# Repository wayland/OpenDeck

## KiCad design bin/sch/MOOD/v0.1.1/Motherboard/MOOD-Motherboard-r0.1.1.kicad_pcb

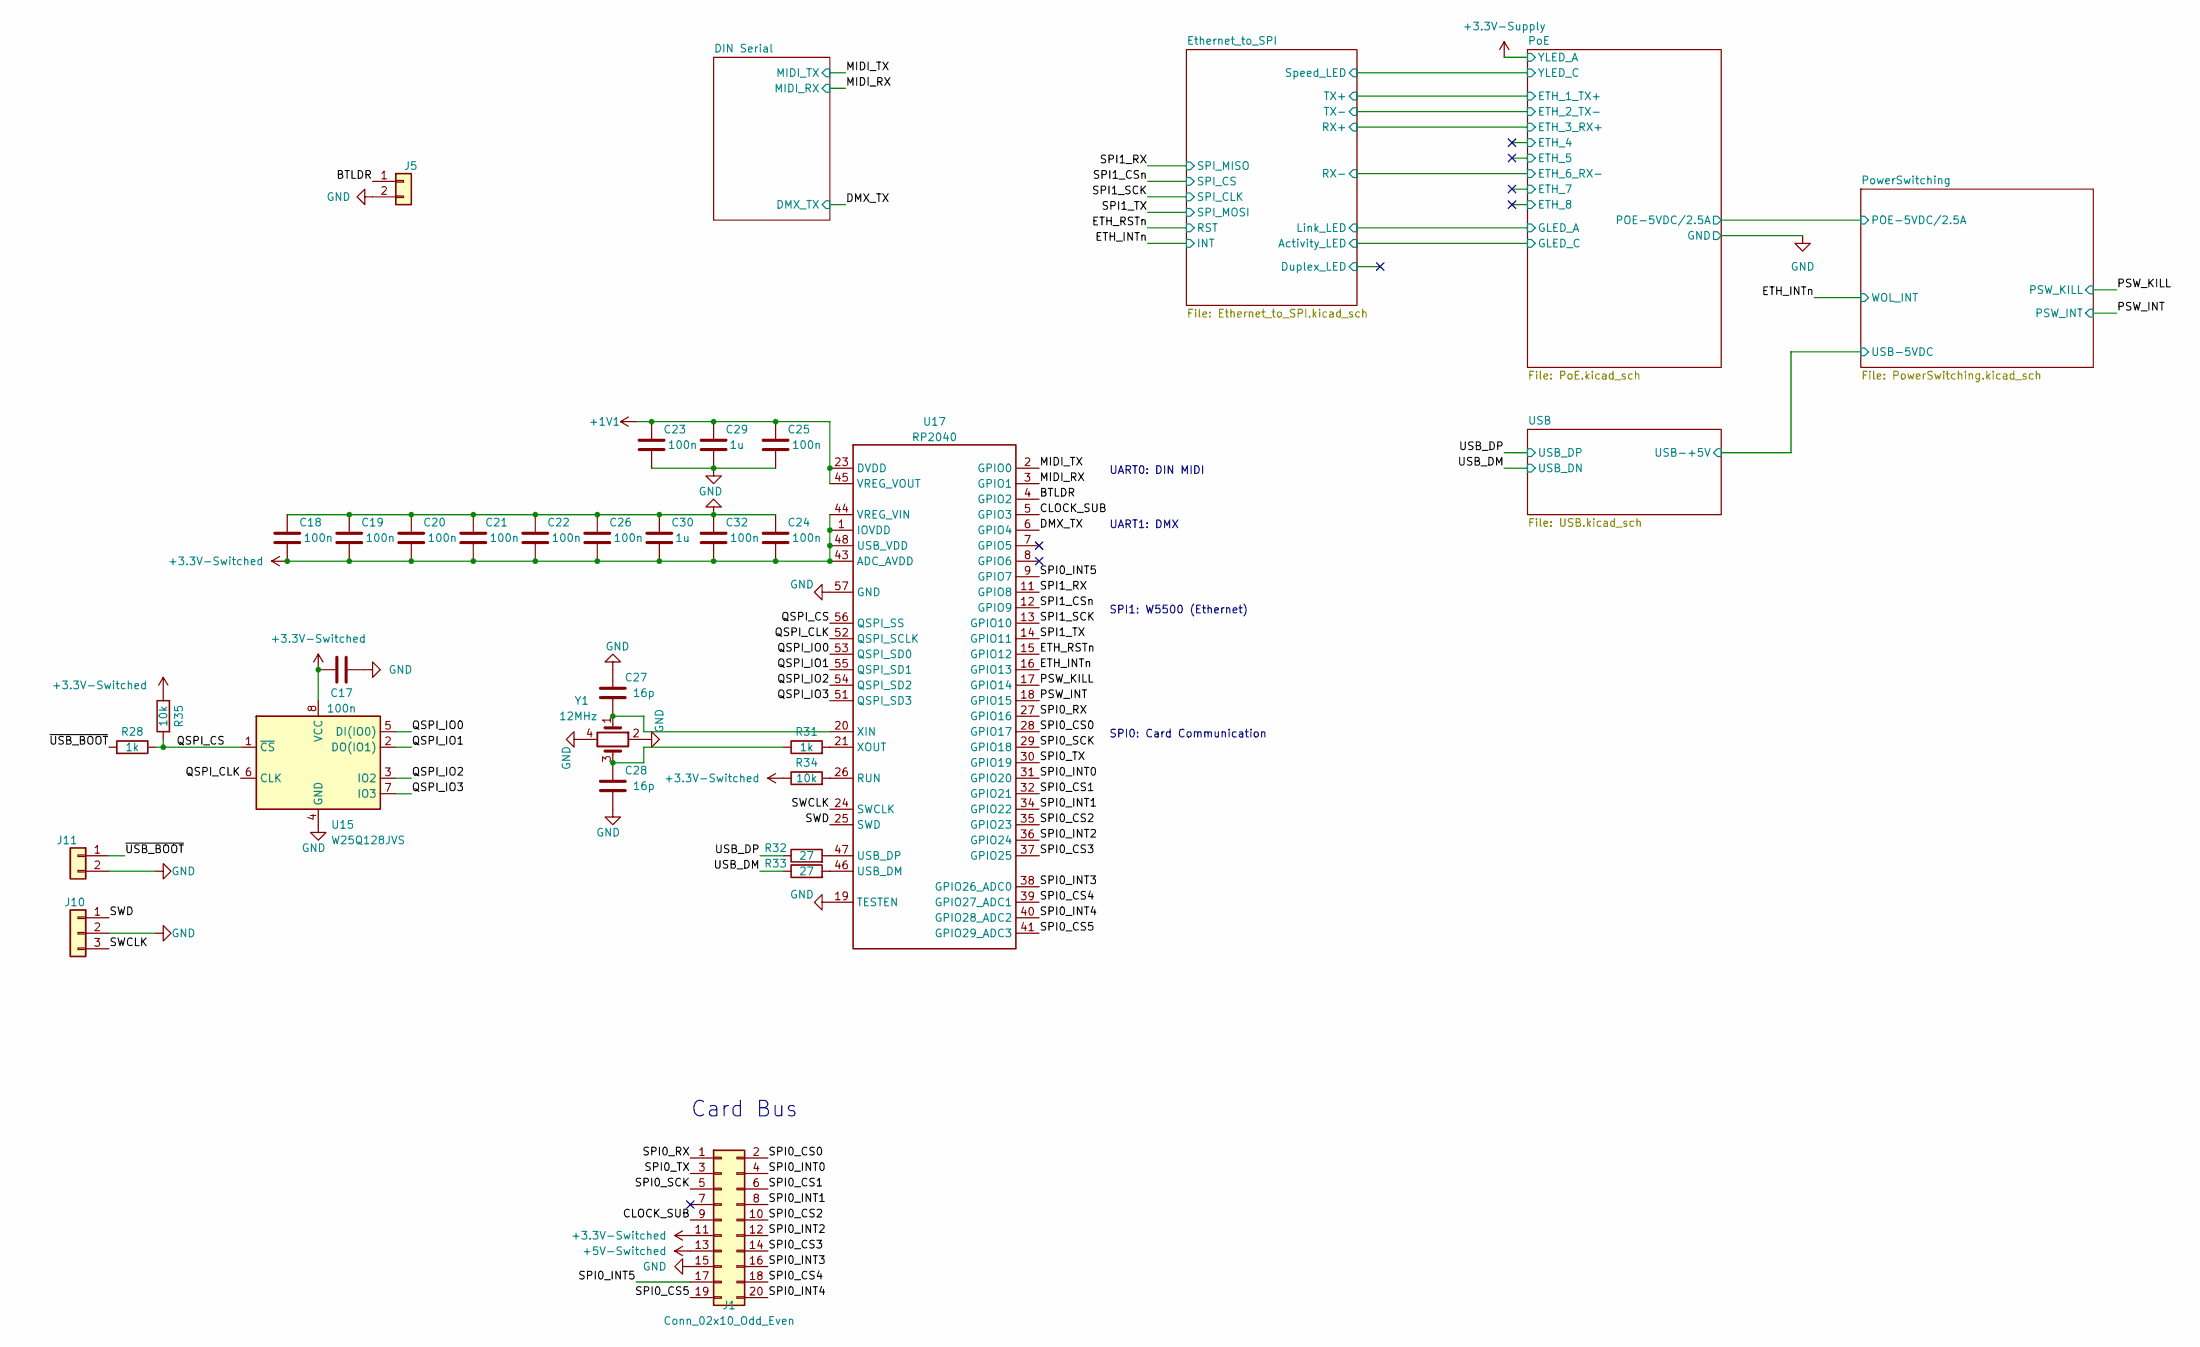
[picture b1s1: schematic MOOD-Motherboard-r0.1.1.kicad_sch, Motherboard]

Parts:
C17, C18, C19, C20, C21, C22, C23, C24, C25, C26, C32: 100n; C_0402_1005Metric; LCSC C1525
C27, C28: 16p; C_0402_1005Metric; LCSC C161307
C29, C30: 1u; C_0402_1005Metric; LCSC C52923
J1: Conn_02x10_Odd_Even; PinHeader_2x10_P2.54mm_Vertical
J5, J11: Conn_01x02; PinHeader_1x02_P2.54mm_Vertical
J10: Conn_01x03; PinHeader_1x03_P2.54mm_Vertical
R28, R31: 1k; R_0402_1005Metric; LCSC C11702
R32, R33: 27; R_0402_1005Metric; LCSC C25100
R34, R35: 10k; R_0402_1005Metric; LCSC C25744
U15: W25Q128JVS; SOIC-8_5.23x5.23mm_P1.27mm
U17: RP2040; QFN-56-1EP_7x7mm_P0.4mm_EP3.2x3.2mm; LCSC C2040
Y1: 12MHz; Crystal_SMD_2520-4Pin_2.5x2.0mm; LCSC C254355

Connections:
+1V1: C23.2, C25.2, C29.2, U17.23 (DVDD), U17.45 (VREG_VOUT), U17.50 (DVDD)
+3.3V-Switched: C17.1, C18.1, C19.1, C20.1, C21.1, C22.1, C24.1, C26.1, C30.1, C32.1, J1.11, R34.1, R35.1, U15.8 (VCC), U17.1 (IOVDD), U17.10 (IOVDD), U17.22 (IOVDD), U17.33 (IOVDD), U17.42 (IOVDD), U17.43 (ADC_AVDD), U17.44 (VREG_VIN), U17.48 (USB_VDD), U17.49 (IOVDD); also elsewhere on the board
+5V-Switched: J1.13; also elsewhere on the board
/BTLDR: J5.1, U17.4 (GPIO2)
/CLOCK_SUB: J1.9, U17.5 (GPIO3)
/DMX_TX: U17.6 (GPIO4); also elsewhere on the board
/ETH_INTn: U17.16 (GPIO13); also elsewhere on the board
/ETH_RSTn: U17.15 (GPIO12); also elsewhere on the board
/MIDI_RX: U17.3 (GPIO1); also elsewhere on the board
/MIDI_TX: U17.2 (GPIO0); also elsewhere on the board
/PSW_INT: U17.18 (GPIO15); also elsewhere on the board
/PSW_KILL: U17.17 (GPIO14); also elsewhere on the board
/QSPI_CLK: U15.6 (CLK), U17.52 (QSPI_SCLK)
/QSPI_CS: R28.1, R35.2, U15.1 (~CS), U17.56 (QSPI_SS)
/QSPI_IO0: U15.5 (DI(IO0)), U17.53 (QSPI_SD0)
/QSPI_IO1: U15.2 (DO(IO1)), U17.55 (QSPI_SD1)
/QSPI_IO2: U15.3 (IO2), U17.54 (QSPI_SD2)
/QSPI_IO3: U15.7 (IO3), U17.51 (QSPI_SD3)
/SPI0_CS0: J1.2, U17.28 (GPIO17)
/SPI0_CS1: J1.6, U17.32 (GPIO21)
/SPI0_CS2: J1.10, U17.35 (GPIO23)
/SPI0_CS3: J1.14, U17.37 (GPIO25)
/SPI0_CS4: J1.18, U17.39 (GPIO27_ADC1)
/SPI0_CS5: J1.19, U17.41 (GPIO29_ADC3)
/SPI0_INT0: J1.4, U17.31 (GPIO20)
/SPI0_INT1: J1.8, U17.34 (GPIO22)
/SPI0_INT2: J1.12, U17.36 (GPIO24)
/SPI0_INT3: J1.16, U17.38 (GPIO26_ADC0)
/SPI0_INT4: J1.20, U17.40 (GPIO28_ADC2)
/SPI0_INT5: J1.17, U17.9 (GPIO7)
/SPI0_RX: J1.1, U17.27 (GPIO16)
/SPI0_SCK: J1.5, U17.29 (GPIO18)
/SPI0_TX: J1.3, U17.30 (GPIO19)
/SPI1_CSn: U17.12 (GPIO9); also elsewhere on the board
/SPI1_RX: U17.11 (GPIO8); also elsewhere on the board
/SPI1_SCK: U17.13 (GPIO10); also elsewhere on the board
/SPI1_TX: U17.14 (GPIO11); also elsewhere on the board
/SWCLK: J10.3, U17.24 (SWCLK)
/SWD: J10.1, U17.25 (SWD)
/USB_DM: R33.1; also elsewhere on the board
/USB_DP: R32.1; also elsewhere on the board
/~USB_BOOT: J11.1, R28.2
unnamed: C27.1, U17.20 (XIN), Y1.1
unnamed: C28.2, R31.1, Y1.3
unnamed: R31.2, U17.21 (XOUT)
unnamed: R32.2, U17.47 (USB_DP)
unnamed: R33.2, U17.46 (USB_DM)
unnamed: R34.2, U17.26 (RUN)

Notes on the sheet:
Card Bus
UART1: DMX
UART0: DIN MIDI
SPI1: W5500 (Ethernet)
SPI0: Card Communication

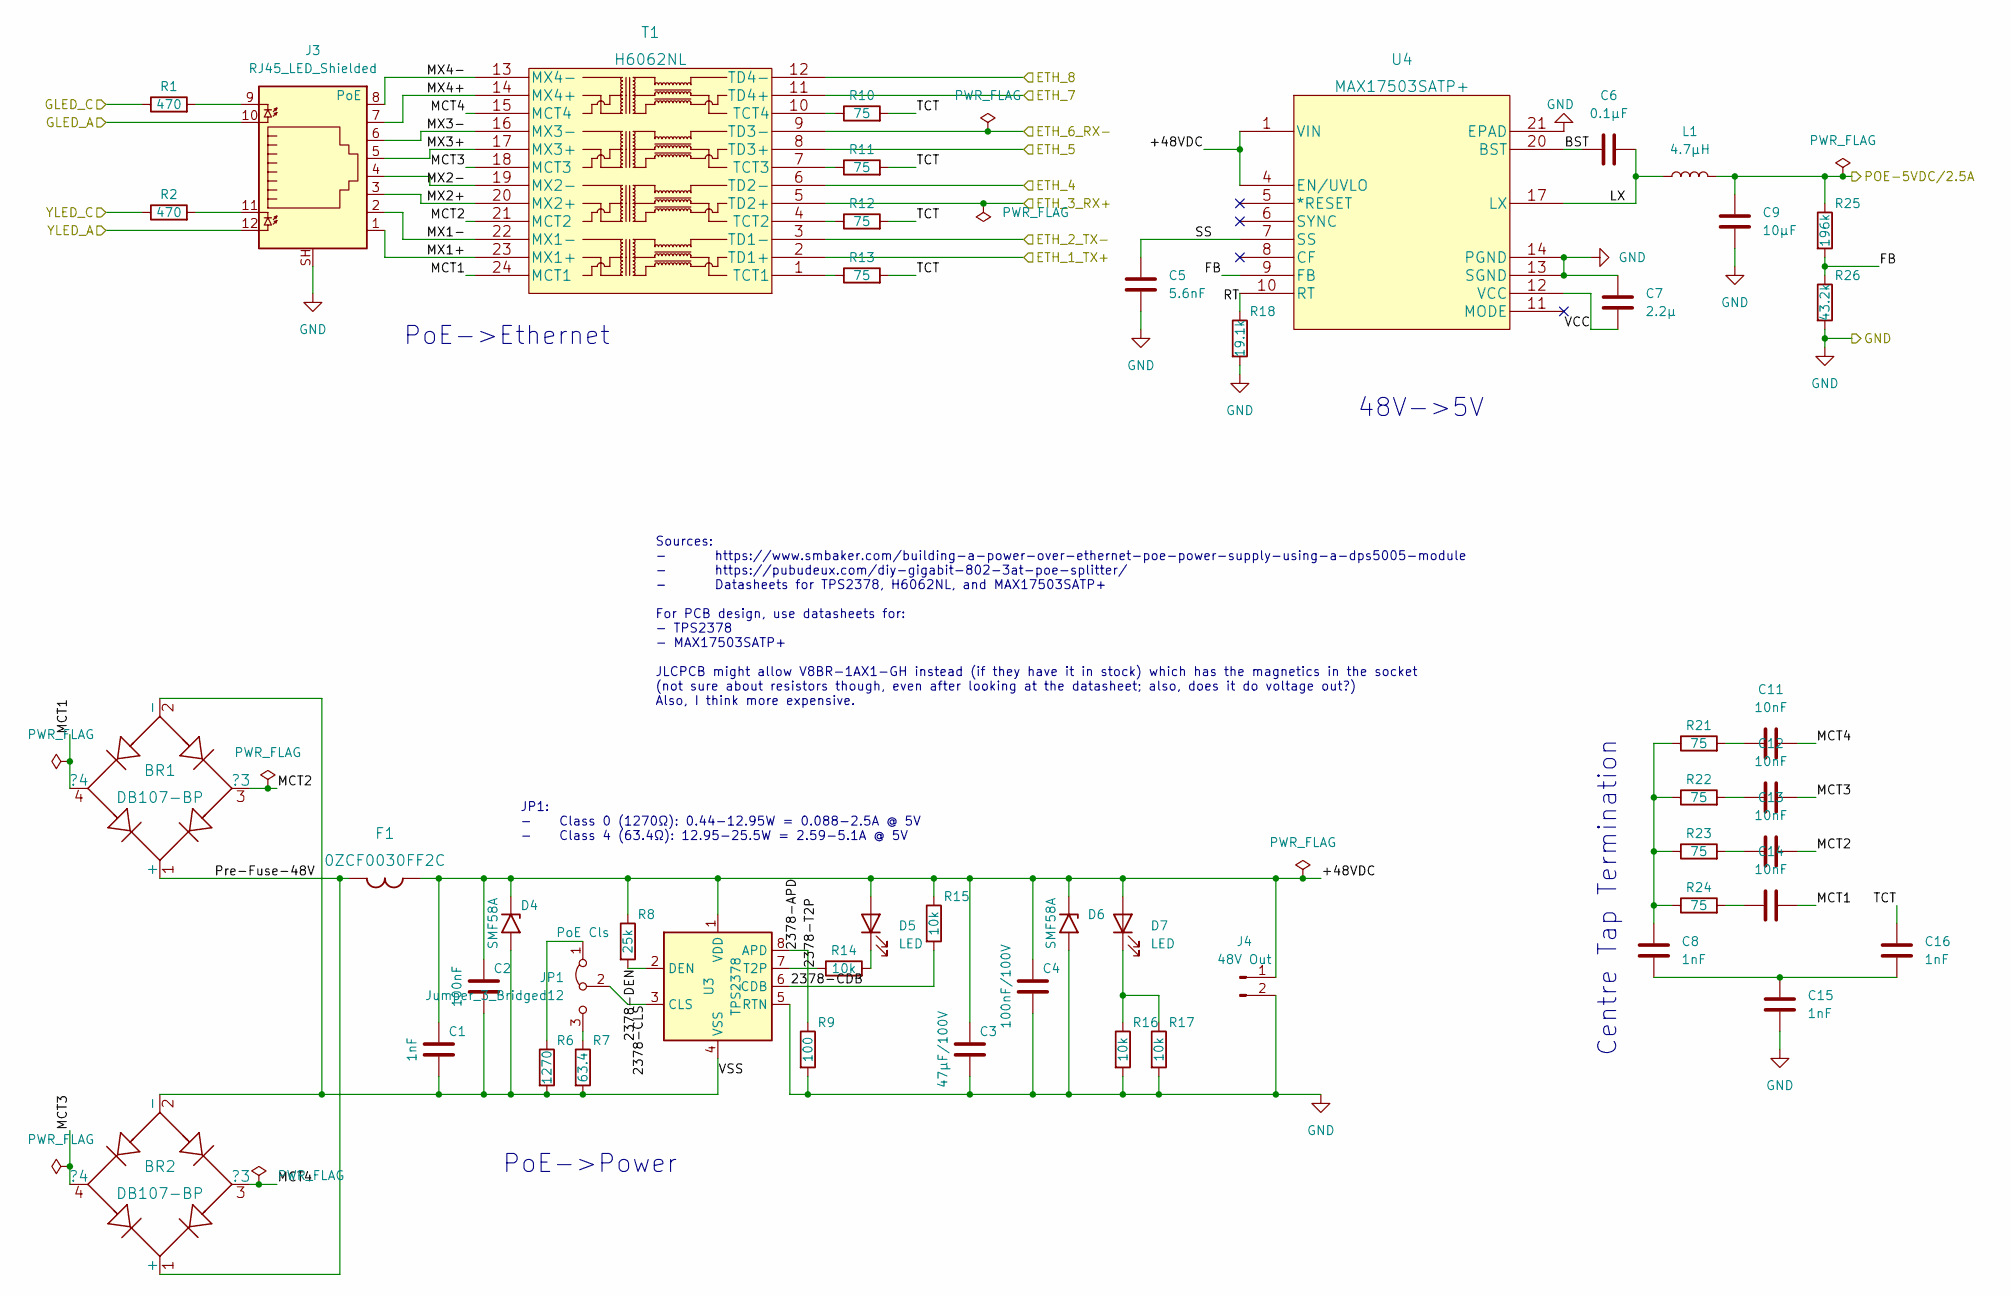
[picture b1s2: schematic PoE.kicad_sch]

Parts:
BR1, BR2: DB107-BP; DB-1_MCC
C1, C8, C15, C16: 1nF; C_0402_1005Metric
C2: 100nF; C_0402_1005Metric
C3: 47μF/100V; C_0402_1005Metric
C4: 100nF/100V; C_0402_1005Metric
C5: 5.6nF; C_0402_1005Metric
C6: 0.1μF; C_0402_1005Metric
C7: 2.2μ; C_0402_1005Metric
C9: 10μF; C_0402_1005Metric
C11, C12, C13, C14: 10nF; C_0402_1005Metric
D4, D6: SMF58A; D_SMF
D5, D7: LED; LED_0805_2012Metric
F1: 0ZCF0030FF2C
J3: RJ45_LED_Shielded; RJ45_BEL_SS74301-00x_Vertical
J4: 48V Out; PinHeader_1x02_P2.54mm_Vertical
JP1: Jumper_3_Bridged12; PinHeader_1x03_P2.54mm_Vertical
L1: 4.7μH; L_0201_0603Metric
R1, R2: 470; R_0402_1005Metric
R6: 1270; R_0402_1005Metric
R7: 63.4; R_0402_1005Metric
R8: 25k; R_0402_1005Metric
R9: 100; R_0402_1005Metric
R10, R11, R12, R13, R21, R22, R23, R24: 75; R_0402_1005Metric
R14, R15, R16, R17: 10k; R_0402_1005Metric
R18: 19.1k; R_0402_1005Metric
R25: 196k; R_0402_1005Metric
R26: 43.2k; R_0402_1005Metric
T1: H6062NL; H6062FNLT_PUL
U3: TPS2378; Texas_HSOP-8-1EP_3.9x4.9mm_P1.27mm_ThermalVias
U4: MAX17503SATP+; 21-100172_T2044+4C_MXM

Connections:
+3.3V-Supply: J3.12; also elsewhere on the board
/Ethernet_to_SPI/Activity_LED: R1.1; also elsewhere on the board
/Ethernet_to_SPI/Link_LED: J3.10; also elsewhere on the board
/Ethernet_to_SPI/RX+: T1.5 (TD2+); also elsewhere on the board
/Ethernet_to_SPI/RX-: T1.9 (TD3-); also elsewhere on the board
/Ethernet_to_SPI/Speed_LED: R2.1; also elsewhere on the board
/Ethernet_to_SPI/TX+: T1.2 (TD1+); also elsewhere on the board
/Ethernet_to_SPI/TX-: T1.3 (TD1-); also elsewhere on the board
/PoE/2378-APD: R9.1, U3.8 (APD)
/PoE/2378-CDB: R15.2, U3.6 (CDB)
/PoE/2378-CLS: JP1.2 (C), U3.3 (CLS)
/PoE/2378-DEN: R8.2, U3.2 (DEN)
/PoE/2378-T2P: R14.1, U3.7 (T2P)
/PoE/+48VDC: C1.1, C2.1, C3.1, C4.1, D4.1 (A1), D5.2 (A), D6.1 (A1), D7.2 (A), F1.2, J4.1, R8.1, R15.1, U3.1 (VDD), U4.1 (VIN), U4.2 (VIN), U4.3 (VIN), U4.4 (EN/UVLO)
/PoE/BST: C6.1, U4.20 (BST)
/PoE/ETH_4: T1.6 (TD2-)
/PoE/ETH_5: T1.8 (TD3+)
/PoE/ETH_7: T1.11 (TD4+)
/PoE/ETH_8: T1.12 (TD4-)
/PoE/FB: R25.2, R26.1, U4.9 (FB)
/PoE/LX: C6.2, L1.1, U4.17 (LX), U4.18 (LX), U4.19 (LX)
/PoE/MCT1: BR1.4 (?4), C14.2, T1.24 (MCT1)
/PoE/MCT2: BR1.3 (?3), C13.2, T1.21 (MCT2)
/PoE/MCT3: BR2.4 (?4), C12.2, T1.18 (MCT3)
/PoE/MCT4: BR2.3 (?3), C11.2, T1.15 (MCT4)
/PoE/MX1+: J3.1, T1.23 (MX1+)
/PoE/MX1-: J3.2, T1.22 (MX1-)
/PoE/MX2+: J3.3, T1.20 (MX2+)
/PoE/MX2-: J3.4, T1.19 (MX2-)
/PoE/MX3+: J3.5, T1.17 (MX3+)
/PoE/MX3-: J3.6, T1.16 (MX3-)
/PoE/MX4+: J3.7, T1.14 (MX4+)
/PoE/MX4-: J3.8, T1.13 (MX4-)
/PoE/POE-5VDC/2.5A: C9.1, L1.2, R25.1; also elsewhere on the board
/PoE/Pre-Fuse-48V: BR1.1 (+), BR2.1 (+), F1.1
/PoE/RT: R18.1, U4.10 (RT)
/PoE/SS: C5.1, U4.7 (SS)
/PoE/TCT: C16.1, R10.2, R11.2, R12.2, R13.2
/PoE/VCC: C7.2, U4.12 (VCC)
EPAD: BR1.2 (-), BR2.2 (-), C1.2, C2.2, D4.2 (A2), R6.2, R7.2, U3.4 (VSS), U3.9 (EPAD)
unnamed: C8.1, R21.1, R22.1, R23.1, R24.1
unnamed: C11.1, R21.2
unnamed: C12.1, R22.2
unnamed: C13.1, R23.2
unnamed: C14.1, R24.2
unnamed: C8.2, C15.1, C16.2
unnamed: D5.1 (K), R14.2
unnamed: D7.1 (K), R16.1, R17.1
unnamed: J3.9, R1.2
unnamed: J3.11, R2.2
unnamed: JP1.1 (A), R6.1
unnamed: JP1.3 (B), R7.1
unnamed: R10.1, T1.10 (TCT4)
unnamed: R11.1, T1.7 (TCT3)
unnamed: R12.1, T1.4 (TCT2)
unnamed: R13.1, T1.1 (TCT1)

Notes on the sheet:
PoE->Power
Sources: - https://www.smbaker.com/building-a-power-over-ethernet-poe-power-supply-using-a-dps5005-module - https://pubudeux.com/diy-gigabit-802-3at-poe-splitter/ - Datasheets for TPS2378, H6062NL, and MAX17503SATP+ For PCB design, use datasheets for: - TPS2378 - MAX17503SATP+ JLCPCB might allow V8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
JP1: - Class 0 (1270Ω): 0.44-12.95W = 0.088-2.5A @ 5V - Class 4 (63.4Ω): 12.95-25.5W = 2.59-5.1A @ 5V
48V->5V
Centre Tap Termination
PoE->Ethernet

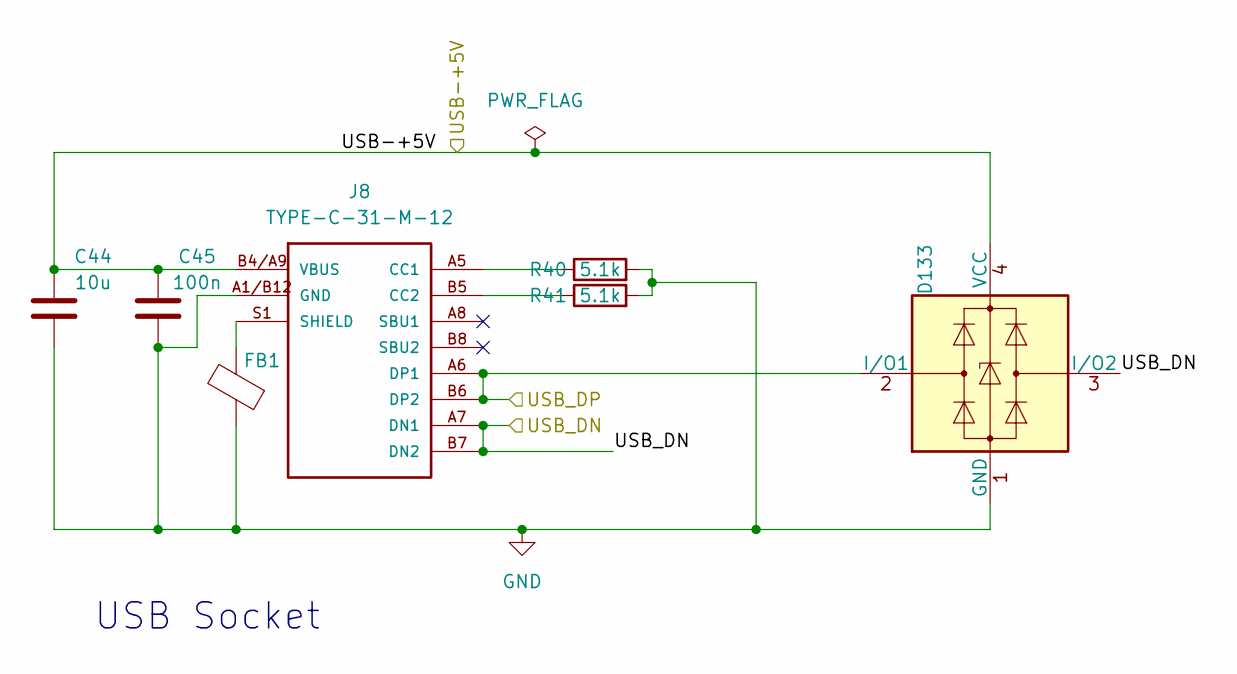
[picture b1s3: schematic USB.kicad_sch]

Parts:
C44: 10u; C_0402_1005Metric; LCSC C15525
C45: 100n; C_0402_1005Metric; LCSC C1525
D133: PRTR5V0U2X; SOT-143; LCSC C2827688
FB1: FerriteBead; R_0805_2012Metric; LCSC C85840
J8: TYPE-C-31-M-12; PARTREV 2020.12.08; LCSC C165948
R40, R41: 5.1k; R_0402_1005Metric; LCSC C25905

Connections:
/USB_DM: D133.3 (I/O2), J8.A7 (DN1), J8.B7 (DN2); also elsewhere on the board
/USB_DP: D133.2 (I/O1), J8.A6 (DP1), J8.B6 (DP2); also elsewhere on the board
unnamed: FB1.2, J8.S1 (SHIELD), J8.S2 (SHIELD), J8.S3 (SHIELD), J8.S4 (SHIELD)
unnamed: J8.A5 (CC1), R40.1
unnamed: J8.B5 (CC2), R41.1
VBUS: C44.2, C45.2, D133.4 (VCC), J8.A4/B9 (VBUS), J8.B4/A9 (VBUS); also elsewhere on the board

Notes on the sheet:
USB Socket

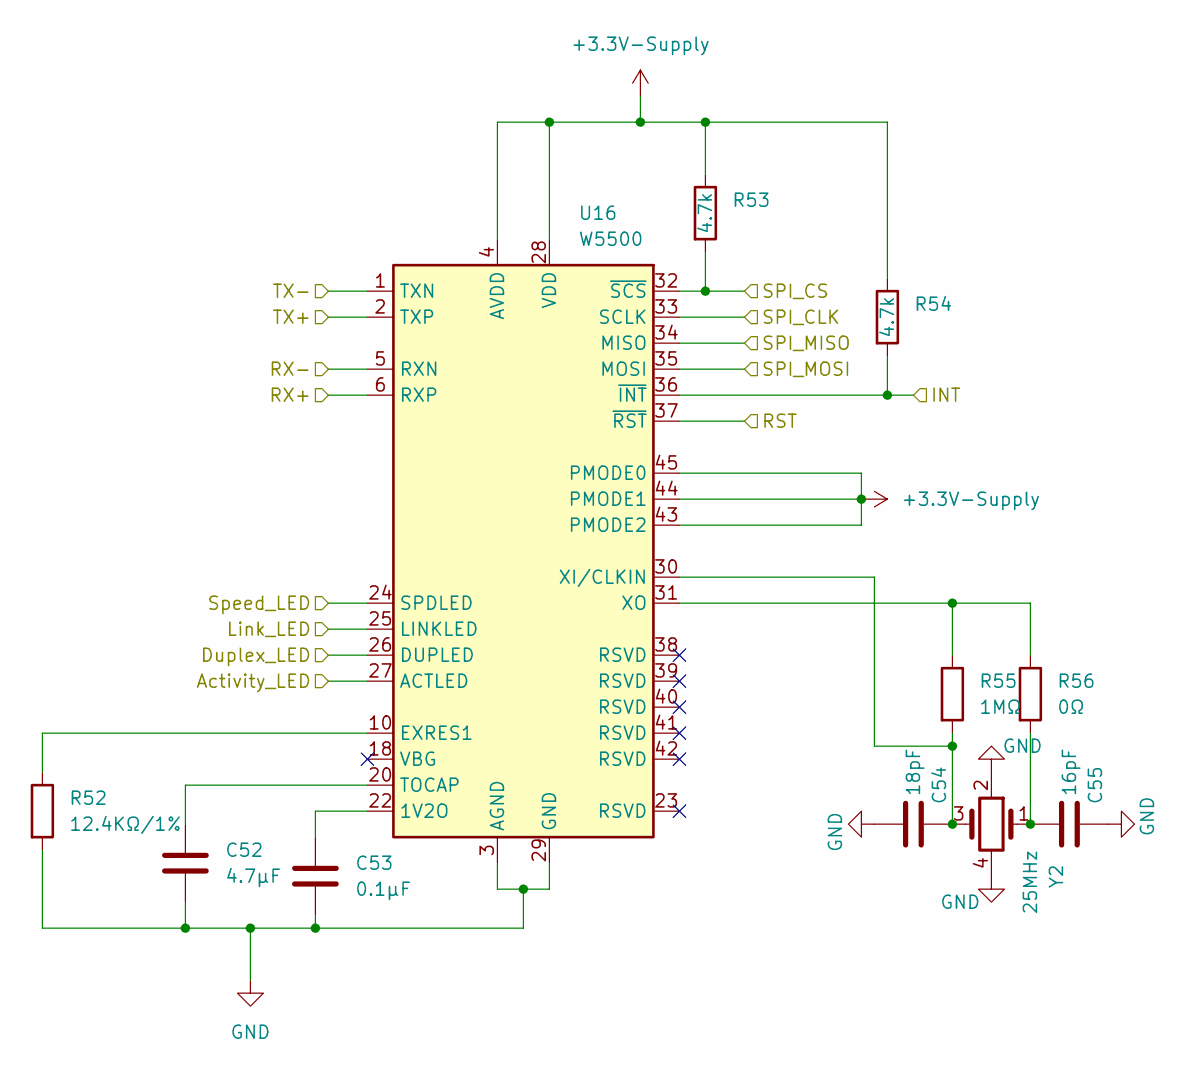
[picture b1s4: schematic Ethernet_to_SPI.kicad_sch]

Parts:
C52: 4.7μF; C_0402_1005Metric
C53: 0.1μF; C_0402_1005Metric
C54: 18pF; C_0402_1005Metric; LCSC C161307
C55: 16pF; C_0402_1005Metric; LCSC C161307
R52: 12.4KΩ/1%; R_0402_1005Metric
R53, R54: 4.7k; R_0402_1005Metric
R55: 1MΩ; R_0402_1005Metric
R56: 0Ω; R_0402_1005Metric
U16: W5500; LQFP-48_7x7mm_P0.5mm
Y2: 25MHz; Crystal_SMD_2520-4Pin_2.5x2.0mm; LCSC C254355

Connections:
+3.3V-Supply: R53.1, R54.1, U16.4 (AVDD), U16.8 (AVDD), U16.11 (AVDD), U16.15 (AVDD), U16.17 (AVDD), U16.21 (AVDD), U16.28 (VDD), U16.43 (PMODE2), U16.44 (PMODE1), U16.45 (PMODE0); also elsewhere on the board
/ETH_INTn: R54.2, U16.36 (~INT); also elsewhere on the board
/ETH_RSTn: U16.37 (~RST); also elsewhere on the board
/Ethernet_to_SPI/Activity_LED: U16.27 (ACTLED); also elsewhere on the board
/Ethernet_to_SPI/Duplex_LED: U16.26 (DUPLED)
/Ethernet_to_SPI/Link_LED: U16.25 (LINKLED); also elsewhere on the board
/Ethernet_to_SPI/RX+: U16.6 (RXP); also elsewhere on the board
/Ethernet_to_SPI/RX-: U16.5 (RXN); also elsewhere on the board
/Ethernet_to_SPI/Speed_LED: U16.24 (SPDLED); also elsewhere on the board
/Ethernet_to_SPI/TX+: U16.2 (TXP); also elsewhere on the board
/Ethernet_to_SPI/TX-: U16.1 (TXN); also elsewhere on the board
/SPI1_CSn: R53.2, U16.32 (~SCS); also elsewhere on the board
/SPI1_RX: U16.34 (MISO); also elsewhere on the board
/SPI1_SCK: U16.33 (SCLK); also elsewhere on the board
/SPI1_TX: U16.35 (MOSI); also elsewhere on the board
unnamed: C52.1, U16.20 (TOCAP)
unnamed: C53.1, U16.22 (1V2O)
unnamed: C54.2, R55.2, U16.30 (XI/CLKIN), Y2.3
unnamed: C55.1, R56.2, Y2.1
unnamed: R52.1, U16.10 (EXRES1)
unnamed: R55.1, R56.1, U16.31 (XO)

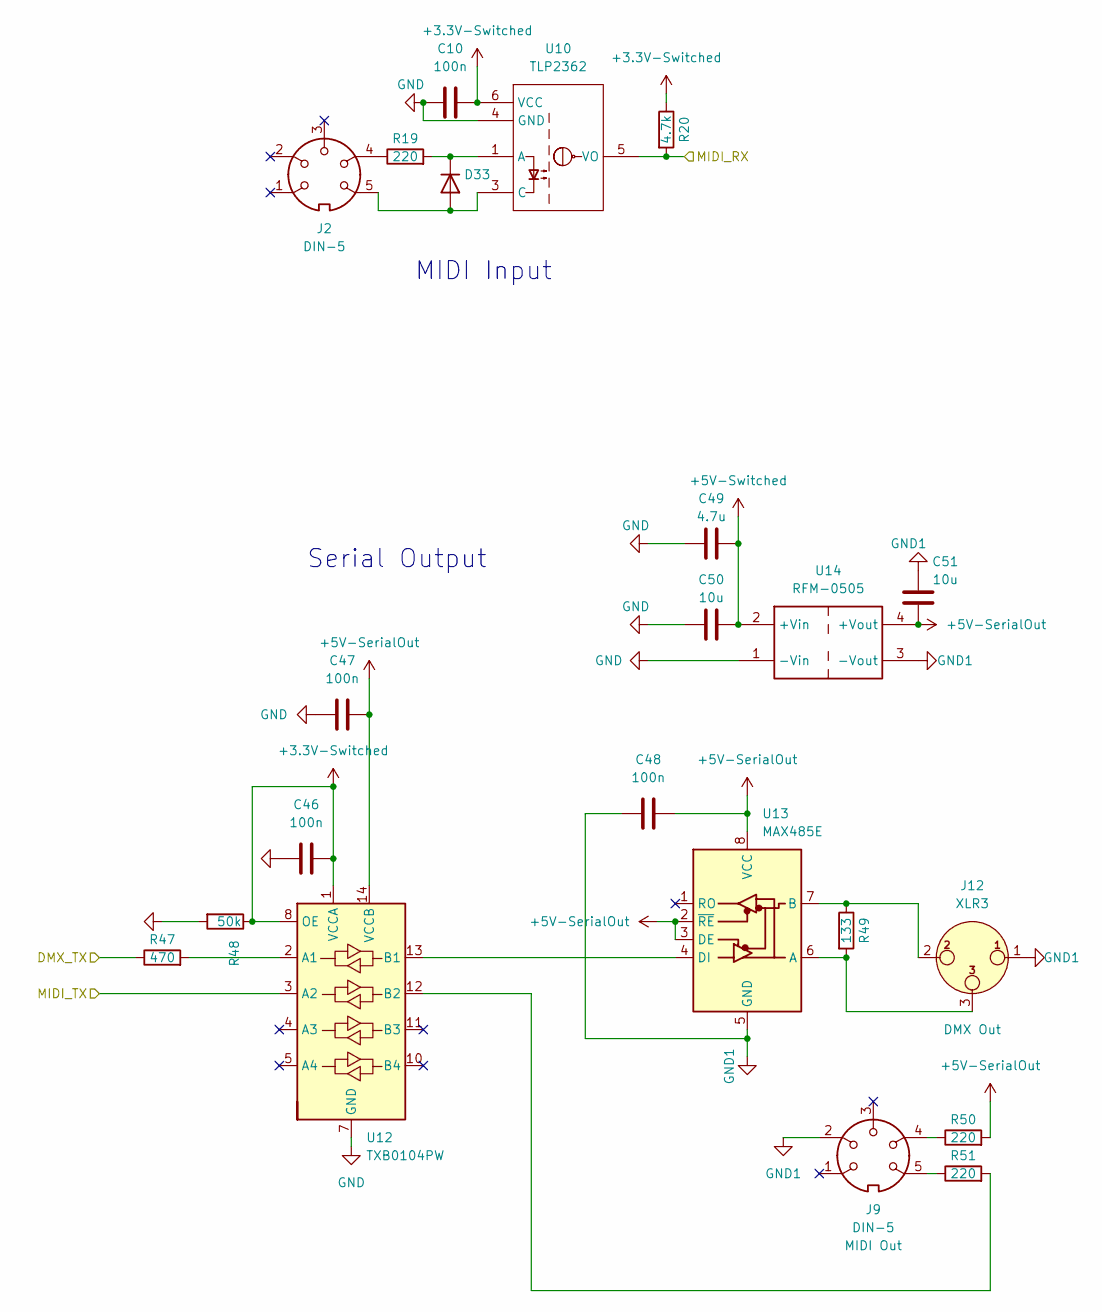
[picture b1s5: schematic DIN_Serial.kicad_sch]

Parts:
C10, C46, C47, C48: 100n; C_0402_1005Metric; LCSC C1525
C49: 4.7u; C_0402_1005Metric; LCSC C23733
C50: 10u; C_0402_1005Metric; LCSC C23733
C51: 10u; C_0402_1005Metric; LCSC C15525
D33: 1N4148WT; D_SOD-523; LCSC C232841
J2, J9: DIN-5; DIN5
J12: XLR3; TRAPC3MX
R19: 220; R_0402_1005Metric; LCSC C25091
R20: 4.7k; R_0402_1005Metric; LCSC C25900
R47: 470; R_0402_1005Metric; LCSC C25117
R48: 50k; R_0402_1005Metric
R49: 133; R_0402_1005Metric; LCSC C497125
R50: 220; R_0402_1005Metric; LCSC C25105
R51: 220; R_0402_1005Metric; LCSC C25077
U10: TLP2362; SO-5_4.4x3.6mm_P1.27mm; LCSC C37658
U12: TXB0104PW; TSSOP-14_4.4x5mm_P0.65mm
U13: MAX485E; SOIC-8_3.9x4.9mm_P1.27mm
U14: RFM-0505; LCSC C131038

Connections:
+3.3V-Switched: C10.2, C46.2, R20.1, R48.1, U10.6 (VCC), U12.1 (VCCA), U12.8 (OE); also elsewhere on the board
+5V-SerialOut: C47.2, C48.2, C51.2, R50.2, U12.14 (VCCB), U13.2 (~RE), U13.3 (DE), U13.8 (VCC), U14.4 (+Vout)
+5V-Switched: C49.2, C50.2, U14.2 (+Vin); also elsewhere on the board
/DMX_TX: R47.1; also elsewhere on the board
/MIDI_RX: R20.2, U10.5 (VO); also elsewhere on the board
/MIDI_TX: U12.3 (A2); also elsewhere on the board
GND1: C48.1, C51.1, J9.2, J12.1, U13.5 (GND), U14.3 (-Vout)
unnamed: D33.1 (K), R19.2, U10.1 (A)
unnamed: D33.2 (A), J2.5, U10.3 (C)
unnamed: J2.4, R19.1
unnamed: J9.4, R50.1
unnamed: J9.5, R51.1
unnamed: J12.2, R49.1, U13.7 (B)
unnamed: J12.3, R49.2, U13.6 (A)
unnamed: R47.2, U12.2 (A1)
unnamed: R51.2, U12.12 (B2)
unnamed: U12.13 (B1), U13.4 (DI)

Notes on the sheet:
MIDI Input
Serial Output

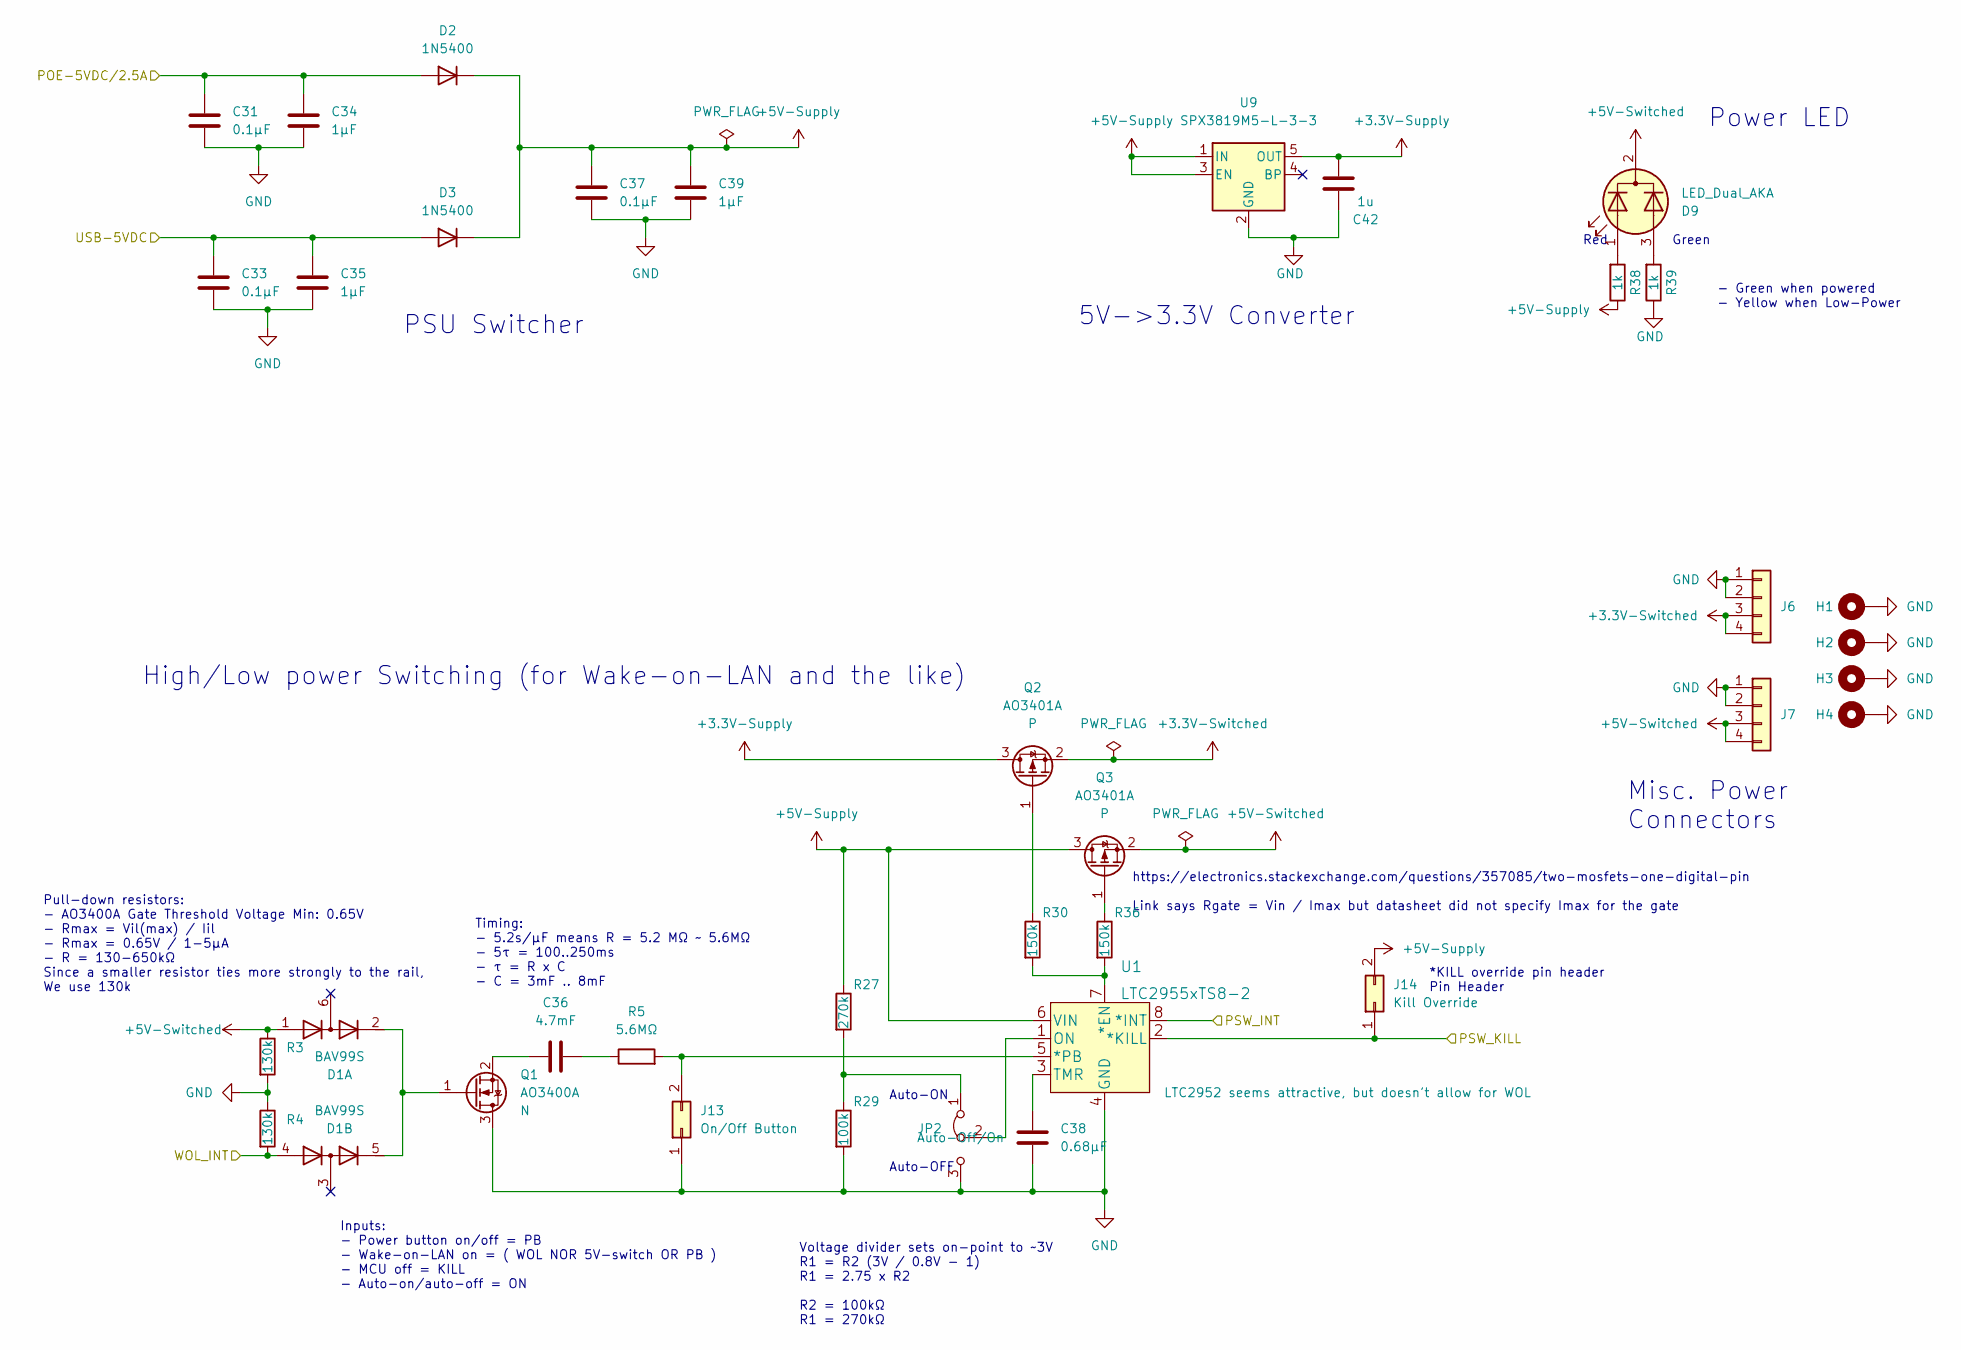
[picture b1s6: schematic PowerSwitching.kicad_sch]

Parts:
C31, C33, C37: 0.1μF; C_0402_1005Metric
C34, C35, C39: 1μF; C_0402_1005Metric
C36: 4.7mF; C_0402_1005Metric
C38: 0.68μF; C_0402_1005Metric
C42: 1u; C_0402_1005Metric; LCSC C52923
D1: BAV99S; SOT-363_SC-70-6
D2, D3: 1N5400; D_DO-201AD_P15.24mm_Horizontal
D9: LED_Dual_AKA; LED-L1T2_LUMILEDS
H1, H2, H3, H4: MountingHole_Pad; MountingHole_3.2mm_M3_DIN965_Pad
J6, J7: Conn_01x04; JST_XH_B4B-XH-A_1x04_P2.50mm_Vertical
J13: On/Off Button; PinHeader_2x01_P2.54mm_Vertical
J14: Kill Override; PinHeader_2x01_P2.54mm_Vertical
JP2: Jumper_3_Bridged12; PinHeader_1x03_P2.54mm_Vertical
Q1: AO3400A; SOT-23
Q2, Q3: AO3401A; SOT-23
R3, R4: 130k; R_0402_1005Metric
R5: 5.6MΩ; R_0402_1005Metric
R27: 270k; R_0402_1005Metric
R29: 100k; R_0402_1005Metric
R30, R36: 150k; R_0402_1005Metric
R38, R39: 1k; R_0402_1005Metric; LCSC C11702
U1: LTC2955xTS8-2; TSOT-23-8
U9: SPX3819M5-L-3-3; SOT-23-5

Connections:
+3.3V-Supply: C42.2, Q2.3 (D), U9.5 (OUT); also elsewhere on the board
+3.3V-Switched: J6.3, J6.4, Q2.2 (S); also elsewhere on the board
+5V-Supply: C37.1, C39.1, D2.1 (K), D3.1 (K), J14.2, Q3.3 (D), R27.1, R38.1, U1.6 (VIN), U9.1 (IN), U9.3 (EN)
+5V-Switched: D1.1 (A1), D9.2 (K), J7.3, J7.4, Q3.2 (S), R3.1; also elsewhere on the board
/ETH_INTn: D1.4 (A3), R4.2; also elsewhere on the board
/PSW_INT: U1.8 (*INT); also elsewhere on the board
/PSW_KILL: J14.1, U1.2 (*KILL); also elsewhere on the board
/PoE/POE-5VDC/2.5A: C31.1, C34.1, D2.2 (A); also elsewhere on the board
unnamed: C36.1, Q1.2 (S)
unnamed: C36.2, R5.1
unnamed: C38.1, U1.3 (TMR)
unnamed: D1.2 (K2), D1.5 (K4), Q1.1 (G)
unnamed: D9.1 (A1), R38.2
unnamed: D9.3 (A2), R39.2
unnamed: J13.2, R5.2, U1.5 (*PB)
unnamed: JP2.1 (A), R27.2, R29.1
unnamed: JP2.2 (C), U1.1 (ON)
unnamed: Q2.1 (G), R30.1
unnamed: Q3.1 (G), R36.1
unnamed: R30.2, R36.2, U1.7 (*EN)
VBUS: C33.1, C35.1, D3.2 (A); also elsewhere on the board

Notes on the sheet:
Green
Pull-down resistors: - AO3400A Gate Threshold Voltage Min: 0.65V - Rmax = Vil(max) / Iil - Rmax = 0.65V / 1-5μA - R = 130-650kΩ Since a smaller resistor ties more strongly to the rail, We use 130k
Auto-OFF
High/Low power Switching (for Wake-on-LAN and the like)
Red
https://electronics.stackexchange.com/questions/357085/two-mosfets-one-digital-pin Link says Rgate = Vin / Imax but datasheet did not specify Imax for the gate
Timing: - 5.2s/μF means R = 5.2 MΩ ~ 5.6MΩ - 5τ = 100..250ms - τ = R x C - C = 3mF .. 8mF
- Green when powered - Yellow when Low-Power
Auto-ON
Power LED
Voltage divider sets on-point to ~3V R1 = R2 (3V / 0.8V - 1) R1 = 2.75 x R2 R2 = 100kΩ R1 = 270kΩ
Misc. Power Connectors
*KILL override pin header Pin Header
Inputs: - Power button on/off = PB - Wake-on-LAN on = ( WOL NOR 5V-switch OR PB ) - MCU off = KILL - Auto-on/auto-off = ON
5V->3.3V Converter
PSU Switcher

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
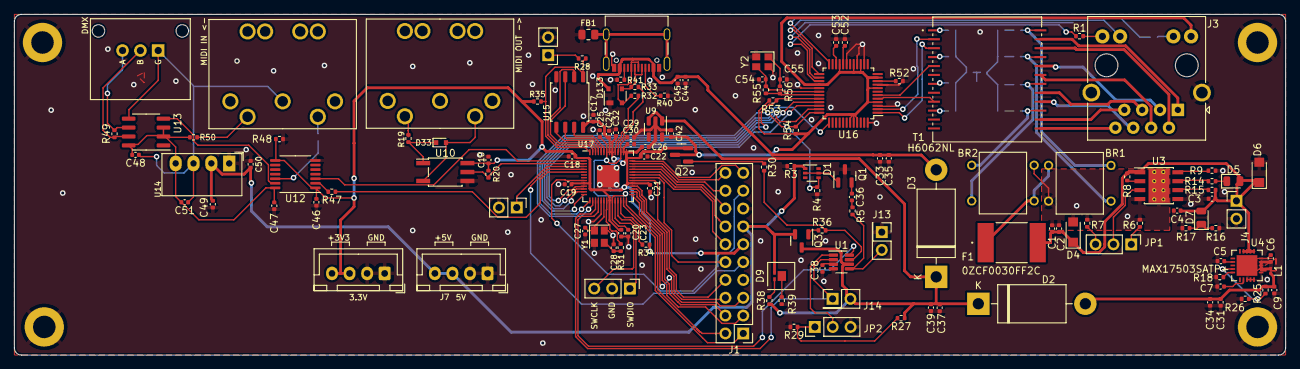
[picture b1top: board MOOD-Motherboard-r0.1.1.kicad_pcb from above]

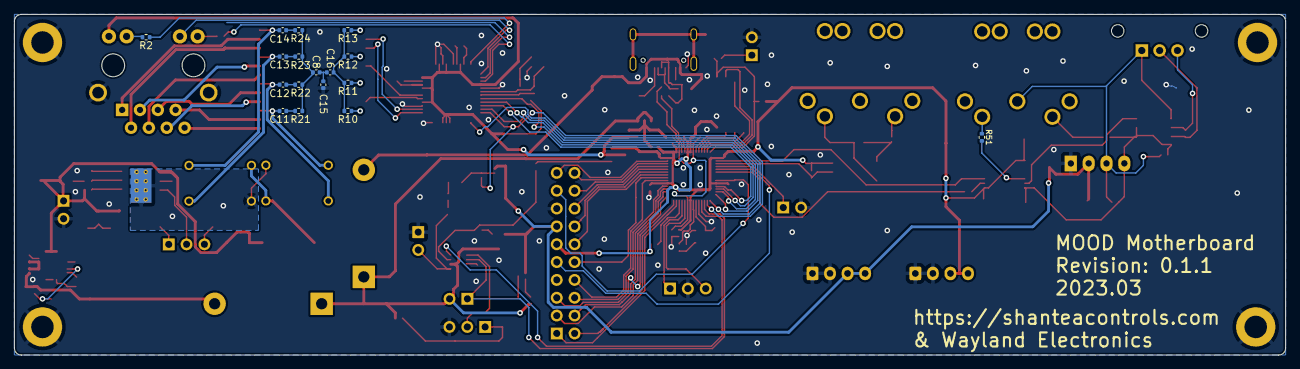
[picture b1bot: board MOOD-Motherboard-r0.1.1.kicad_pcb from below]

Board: 2 copper layers, 181.0 x 48.5 mm, 154 parts (17 on the bottom side), 136 nets.

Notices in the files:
parts and their libraries:
Copyright 2021 Accelerated Designs. All rights reserved.
